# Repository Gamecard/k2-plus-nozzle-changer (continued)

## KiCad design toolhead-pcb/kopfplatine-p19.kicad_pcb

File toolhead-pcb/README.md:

# Kopfplatine P19, Fassung 10 – Toolhead-Platine für den K2-Düsenwechsler

**English summary:** This is the toolhead board for the K2 Plus nozzle changer (prototype 19 v2). It replaces the original
toolhead board, runs from 24–48 V, talks to the Klipper host via CAN bus and additionally provides USB through an on-board
4-port hub (bed camera, Cartographer probe, MCU). It carries an STM32G0B1 MCU, a TMC5160 stepper driver with external MOSFETs,
a 24-bit load-cell ADC, an accelerometer, five low-side outputs and all sensor inputs on 14 locking JST GH connectors.
The KiCad files are produced by a Python generator (`bauen.sh`); Gerber, BOM and CPL files for JLCPCB are included.
Status: not yet manufactured or tested.

Stand: Schaltplan und Layout sind vollständig und bestehen die automatischen Prüfungen; gefertigt oder in Betrieb genommen
wurde die Platine noch nicht. Lizenz und Haftung: [`../LIZENZ-UND-HAFTUNG.md`](../LIZENZ-UND-HAFTUNG.md).

## Aufgabe

Die Platine sitzt hinten am Druckkopf des Düsenwechslers (siehe [`../prototyp-19v2/README.md`](../prototyp-19v2/README.md)) und
ersetzt die Original-Kopfplatine des Creality K2 Plus. Sie steuert alles, was am Kopf selbst sitzt: den Extrudermotor, die
Hubmagnete des Riegels, die Lüfter, den Linienlaser, und sie liest alle Kopfsensoren. Die Heizungen und Temperaturfühler der
Patronen hängen **nicht** an dieser Platine, sondern an einer eigenen Heizplatine (nicht Teil dieses Repositorys).

Eckdaten: 52 × 76,8 mm, 6 Kupferlagen, beidseitig bestückt (230 Teile), Bauhöhe auf der Oberseite höchstens 7,37 mm, auf der
Unterseite flächig höchstens 1,5 mm. Vier Befestigungslöcher für M2 (H1–H4).

**Begriffe:**
- **CAN-Bus:** robuste Zweidraht-Datenleitung (CANH/CANL), über die Klipper mit Zusatzplatinen spricht; an jedem Ende des Busses
  sitzt ein 120-Ω-Abschlusswiderstand.
- **Low-Side-Schalter:** Ein Transistor (MOSFET) schaltet die Minusleitung eines Verbrauchers; die Plusleitung liegt fest an 24 V.
- **Lötbrücke (JP_…):** zwei Lötflächen, die man mit einem Lötzinntropfen verbindet oder mit einem Messer trennt, um eine Option zu wählen.
- **Nutzen (Panel):** Rahmen um die Platine, in dem sie gefertigt und bestückt wird; nach der Bestückung bricht man sie an
  **Haltestegen** mit **Mausbissen** (Reihen kleiner Bohrungen) heraus.

## Blockübersicht

Belege: [`SCHALTUNG.md`](SCHALTUNG.md) (Abschnitte 0f, 0h, 1–11), Schaltplan [`doku/schaltplan.pdf`](doku/schaltplan.pdf),
Stückliste [`fertigung/stueckliste.csv`](fertigung/stueckliste.csv). Bei Widersprüchen gilt der Schaltplan.

| Block | Bauteile | Aufgabe |
|---|---|---|
| **Eingang** | J1 (JST ZE 6-pol.), F1 (SMD-Sicherung 5 A / 63 V), D1 (TVS-Diode SMBJ51A), Dämpfungsglied und Pufferkondensatoren 100 V | Versorgung 24–48 V (höchstens 50 V) und CAN-Bus über einen Stecker. Bei Verpolung leitet D1 und die Sicherung löst aus. Spannungsmessung von VIN an der MCU |
| **24-V-Schiene** | U2 TPS54360 (Abwärtswandler 60 V), L1 33 µH, D3 | erzeugt V24 (≈ 23,8 V) für Hubmagnete, Lüfter, Laser und den 5-V-Wandler; Auslegung 2 A; Spannungsmessung an der MCU |
| **5 V / 3,3 V** | U3 LMR51420 (aus V24), U4 LDO ME6211 3,3 V | V5 für USB-Geräte, CAN-Transceiver und LED-Kette; V3V3 für Logik. Der 3,3-V-Regler wird über ein Dioden-ODER aus V5 oder aus der USB-C-Buchse gespeist (Flashen ohne 24 V); USB-C-Spannung geht nie auf V5. Analoge 3,3 V (AVDD) über Ferrit gefiltert |
| **CAN** | U10 TJA1051T/3, D_CAN (ESD), JP_CAN | CAN-Transceiver an PB0/PB1; 120-Ω-Abschluss über Lötbrücke JP_CAN (Werkzustand offen – schließen, wenn der Kopf Busende ist) |
| **USB-Eingang und Hub** | J44, D8 (ESD), U5 CH334P (4-Port-Hub, 12-MHz-Quarz Y1) | USB vom Steuerrechner über J44 an den Hub-Eingang. Hub-Ports: 1 → MCU (über U11), 2 → Bettkamera J42, 3 → Cartographer J43, 4 frei. VBUS an J44 dient nur der Erkennung „Kabel steckt“; die Geräte werden aus dem eigenen V5 über je eine selbstrückstellende Sicherung (PTC 0,5 A, F2/F3) versorgt |
| **USB-C zum Flashen** | J16 (USB-C liegend), D_C1 (ESD), U11 FSUSB42MUX | Steckt ein PC an J16, schaltet U11 die USB-Leitung der MCU vom Hub auf die USB-C-Buchse um; die MCU kann das am Pin PD3 erkennen |
| **Mikrocontroller** | U1 STM32G0B1RBT6 (LQFP-64), Quarz 8 MHz (Y2), Taster RESET (SW1) und BOOT (SW2), SWD-Messpads | führt Klipper (Firmware-Einstellung „CAN bus on PB0/PB1“ oder USB) |
| **Motortreiber** | U7 TMC5160A-TA, Q1–Q8 CSD19537Q3 (100-V-MOSFETs), R36/R43 0,11-Ω-Messwiderstände, J3 | Schrittmotortreiber mit externen MOSFETs, direkt aus VIN (24–48 V) versorgt; Step/Dir + SPI |
| **Wägezelle (PRTouch)** | U8 ADS1220 (24-bit-ADC), Eingangsfilter, J33 | wertet die Original-Messplatte (Dehnungsmessstreifen) des K2 Plus aus; ratiometrische Messung mit AVDD als Erregung |
| **Beschleunigungssensor** | U9 LIS2DW12 | für Input Shaping, am SPI-Bus |
| **Schaltausgänge** | Q9–Q13 AO3400A, Freilaufdioden, Gate-Pulldowns 100 kΩ | Low-Side für: Hubmagnete (beide gemeinsam), Kopflüfter L, Kopflüfter R, Bauteillüfter, Laser. Alle Ausgänge sind nach einem Reset aus. Laser-Plus über JP_LASER wählbar 5 V oder 24 V |
| **Sensoreingänge** | Hall G1 (digital), Hall G2 (analog + Komparator U13 TLV1701), Eddy-Spule LDC1612 (I²C), Probe/Endstop, 3 Lüfter-Tachos, NTC (Kopftemperatur), ESD-Arrays D18/D19 | Probe-Versorgung über JP_PROBE_V wählbar 5 V (Werk) oder 24 V; der Probe-Eingang verträgt 5 V und 24 V am Signal |
| **LED-Kette** | U12 SN74AHCT1G125 (Pegelwandler 3,3 → 5 V), F_LED (PTC 1,1 A), C_LED, J34 | adressierbare RGB-LEDs (WS2812B/SK6812) als Statusanzeige |
| **Statusanzeige** | D6, D11 (grün), D7, D14 (gelb) | Spannungen, Hubmagnet, Lebenszeichen der MCU |

## Stecker

Lage in mm auf der Bestückungsoberseite, gemessen von der linken oberen Platinenecke (x nach rechts, y nach unten); das ist die
Ansicht **von hinten auf den Kopf**. Alle JST-GH-Stecker (Raster 1,25 mm) liegen flach, rasten ein und nehmen fertig
konfektionierte Kabel auf; Pin 1 ist im Bestückungsdruck mit einem Dreieck markiert. Vollständige Belegung je Pin:
[`SCHALTUNG.md`](SCHALTUNG.md), Abschnitt **0h** (J30–J44) und **0f** (J1, J3, J16).

| Stecker | Typ / Pole | Funktion | Lage x / y, Abgang | Belegung (Kurzform) |
|---|---|---|---|---|
| J1 | JST ZE, 6 | Versorgung 24–48 V + CAN | 42,8 / 6,6, Oberkante | 1, 2 VIN · 3, 4 GND · 5 CANH · 6 CANL |
| J3 | JST ZE, 4 | Extrudermotor | 14,8 / 59,4, unten links | 1 A1 · 2 A2 · 3 B1 · 4 B2 |
| J16 | USB-C, liegend | PC-Anschluss zum Flashen | 8,4 / 3,3, Öffnung über die Oberkante | USB 2.0, CC je 5,1 kΩ |
| J30 | JST GH, 2 | Hubmagnet R | 34,1 / 17,9, Litzen nach oben | 1 +24 V · 2 geschaltet |
| J31 | JST GH, 3 | Hubmagnet L | 42,8 / 15,9, Litzen nach oben | 1 +24 V · 2 geschaltet · 3 frei |
| J32 | JST GH, 3 | Hall G1 (Riegel zu/offen) | 27,2 / 17,5, Litzen nach oben | 1 3,3 V · 2 GND · 3 Signal |
| J33 | JST GH, 4 | Messplatte (PRTouch) | 30,3 / 3,8, Litzen nach oben | 1 E+ · 2 E− · 3 S+ · 4 S− |
| J34 | JST GH, 3 | LED-Kette | 4,4 / 17,5, Litzen nach oben | 1 5 V · 2 GND · 3 Daten |
| J35 | JST GH, 3 | Probe / Endstop | 12,0 / 17,5, Litzen nach oben | 1 Versorgung (5 V / 24 V) · 2 GND · 3 Signal |
| J36 | JST GH, 3 | Kopflüfter R | 19,6 / 17,5, Litzen nach oben | 1 +24 V · 2 geschaltet · 3 Tacho |
| J37 | JST GH, 3 | Kopflüfter L | 24,9 / 66,6, Litzen nach unten | 1 +24 V · 2 geschaltet · 3 Tacho |
| J39 | JST GH, 2 | Linienlaser | 3,3 / 68,9, Litzen nach unten | 1 + (5 V / 24 V) · 2 geschaltet |
| J40 | JST GH, 5 | Eddy-Spule (LDC1612, I²C) | 13,9 / 29,3, Litzen nach unten | 1 3,3 V · 2 GND · 3 SCL · 4 SDA · 5 INTB |
| J41 | JST GH, 6 | Hall G2 (Arm) + Bauteillüfter | 30,9 / 60,6, Litzen nach unten | 1 Hall-Signal · 2 3,3 V · 3 GND · 4 Tacho · 5 geschaltet · 6 +24 V |
| J42 | JST GH, 5 | USB Bettkamera | 33,7 / 66,6, Litzen nach unten | 1 5 V · 2 GND · 3 D− · 4 D+ · 5 GND |
| J43 | JST GH, 5 | USB Cartographer | 42,8 / 70,0, Litzen nach unten | 1 5 V · 2 GND · 3 D− · 4 D+ · 5 GND |
| J44 | JST GH, 5 | USB-Eingang vom Steuerrechner | 19,1 / 3,8, Litzen nach oben | 1 VBUS (nur Erkennung) · 2 GND · 3 D− · 4 D+ · 5 GND |

„geschaltet“ = Minusleitung über den Low-Side-Schalter. J38 ist nicht belegt (die Nummer entfiel).

**Steckreihenfolge** (sonst verdeckt ein Gegenstecker den nächsten): **J39 vor J3**, **J42 vor J37**, **J44 vor J36**.
Alle übrigen Stecker sind in beliebiger Reihenfolge steckbar.

**Achtung:** Eingangsspannung höchstens 50 V (ein 48-V-Netzteil nicht höher drehen). J1 nicht unter Spannung stecken.

## Wegfall des Original-Kopfkabels (J2)

Frühere Fassungen hatten einen Anschluss J2 für das Original-Kopfkabel des K2 Plus. In Fassung 10 ist er **entfallen**, weil sonst
nicht alle Stecker flach und steckbar auf die Platine passten. Folgen:

- Für den Betrieb ist ein **neues Kabel vom Drucker zum Kopf** nötig:
  - an **J1**: Versorgung 24–48 V (2 Adern), GND (2 Adern), CANH, CANL;
  - an **J44**: USB vom Steuerrechner (D+, D−, GND; VBUS nur zur Erkennung).
- Entfallen sind damit auch: Betrieb und 24-V-Einspeisung über das Original-Kopfkabel, die Messpunkte für dessen serielle
  Leitungen und die zugehörigen Auswahl-Widerstände.
- Ist der Kopf das Ende des CAN-Busses, die Lötbrücke **JP_CAN** schließen.

## Kabel

Die Geräteleitungen, ihre Längen im Kopfmodell und empfohlene Fertigkabel stehen in [`doku/KABELLISTE.md`](doku/KABELLISTE.md).
Kurz: JST-GH-Fertigkabel (Gegenstecker GHR-0nV-S, Litze AWG 28), eine Seite mit Stecker, die andere offen zum Anlöten am Gerät.
Neben der Platine (Seitenstreifen 1,5 mm) die Litzen einzeln flach nebeneinander legen, kein rundes Bündel. Längen vor dem Kauf
am gedruckten Kopf nachmessen.

## Fertigung (JLCPCB)

Alle Angaben für das Bestellformular stehen in [`fertigung/bestellangaben.md`](fertigung/bestellangaben.md). Das Wichtigste:

| Punkt | Wert |
|---|---|
| Hochladen | `fertigung/nutzen/kopfplatine-p19-nutzen_gerber_jlcpcb.zip`, dazu `fertigung/nutzen/jlcpcb_bom.csv` und `fertigung/nutzen/jlcpcb_cpl.csv` |
| Nicht hochladen | `fertigung/kopfplatine-p19_gerber_jlcpcb.zip` (Einzelplatine ohne Rand – Stecker stehen näher als 3 mm an der Kante, JLC würde eigene Ränder ansetzen) |
| Lagen / Aufbau | 6 Lagen, Lagenaufbau JLC06161H-7628, 1,6 mm, ENIG, Durchkontaktierungen gefüllt und abgedeckt (Epoxy Filled & Capped) |
| Nutzen | „Panel by Customer“, 71 × 90,8 mm, eine Platine je Nutzen, Frässchlitz 2 mm, 5 Haltestege mit Mausbissen, 3 Passermarken, 3 Werkzeuglöcher |
| Impedanz | USB-Paare auf Lage 3 (In2.Cu) 0,20 mm / 0,15 mm, Ziel 90 Ω differentiell ±10 % (rechnerisch 83–91 Ω; Werkzeug `werkzeuge/zdiff_l3.py`) – JLC rechnet nach und fragt zurück |
| Bestückung | beidseitig, 230 Teile (87 oben, 143 unten), 78 BOM-Zeilen; Röntgenprüfung für Q1–Q8, U5, U9 empfohlen; unbestückt (DNP): C27, C28, C29, R21 |

Vor der Bestellung unbedingt:

- **Bestand des 2-poligen JST-GH-Steckers (LCSC C189893)** für J30 und J39 am Bestelltag prüfen – am 21.11.2026 waren nur 3 Stück
  vorrätig (2 je Platine). Sonst Beschaffung über den Bestücker, Beistellung oder von Hand nachbestücken.
- **Pin 1 und Drehung** aller gepolten Teile in der Bestellvorschau ansehen, besonders die JST-GH-Stecker J30–J44, J1, J3 und die
  Lage von J16. Nur 20 der 230 Teile sind gegen Bibliotheksdaten des Bestückers nachgewiesen
  ([`fertigung/drehung-nachweis.txt`](fertigung/drehung-nachweis.txt), 0 Fehler); die Liste der Teile, die von Hand zu prüfen
  sind, steht in den Bestellangaben, Abschnitt 5. Hilfe: [`fertigung/nutzen/pin1-liste.txt`](fertigung/nutzen/pin1-liste.txt).
- Lagerbestand aller knappen Teile prüfen; einige LCSC-Nummern sind nicht bestätigt (Liste am Ende von
  [`STUECKLISTE.md`](STUECKLISTE.md)).

## Inhalt dieses Ordners

| Pfad | Inhalt |
|---|---|
| `kopfplatine-p19.kicad_pro/_sch/_pcb/_dru` | KiCad-10-Projekt (Schaltplan, geroutete Platine, Zusatzregeln) |
| `kopfplatine_p19.kicad_sym`, `kopfplatine_p19.pretty/`, `fp-lib-table`, `sym-lib-table` | Projektbibliothek (eigene Symbole und Footprints); alles andere aus den KiCad-Standardbibliotheken |
| `SCHALTUNG.md` | pin-genaue Schaltungsvorgabe für den Generator (mit Lesehinweis oben) |
| `STUECKLISTE.md` | Stückliste mit Lagerstand und Bauhöhen (vom Generator erzeugt, Lagerstand vom November 2026) |
| `bauen.sh`, `generator/`, `werkzeuge/` | Generator: erzeugt Schaltplan, Platzierung, Prüfungen und Fertigungsdaten |
| `routing/` | Eingabe (`f10a_a.dsn`) und Ergebnis (`f10a_a.ses`) des gewählten Autorouter-Laufs |
| `fertigung/` | Gerber-ZIPs (Einzelplatine und Nutzen), BOM, CPL, Stückliste, Bestellangaben, Drehungsnachweis, Randabstand, Stege, Nutzen-Prüfung |
| `doku/` | Kabelliste, Schaltplan-PDF, Lagen-PDF, Bestückungsübersicht (PDF/PNG), Bilder, Prüfberichte |
| `klipper/` | Klipper-Beispielkonfiguration (Entwurf, nicht erprobt) |

## Platine neu erzeugen

Die KiCad-Dateien sind **nicht von Hand gezeichnet**, sondern werden von einem Python-Generator erzeugt. Änderungen gehören in
den Generator (`generator/kopfplatine.py` und Module); Änderungen nur in KiCad gehen beim nächsten Lauf verloren.

Benötigt (aus `bauen.sh` und dem Generator abgelesen):

- **KiCad 10** mit `kicad-cli` und dem Python-Modul `pcbnew` (Fertigungsdaten erstellt mit KiCad 10.0.8), KiCad-Standardbibliotheken
  in den üblichen Pfaden (`/usr/share/kicad/…`, Variablen `KICAD10_*`);
- **Python 3** mit `numpy` und `Pillow`;
- **rsvg-convert** (librsvg) für die Bilder;
- **gcc** (optional; beschleunigt die Wegsuche, sonst läuft eine Python-Fassung);
- **Freerouting** für das Routing (wird nicht von `bauen.sh` aufgerufen).

Ablauf:

```sh
cd toolhead-pcb
./bauen.sh                               # Schaltplan, ERC, Netzliste, Stückliste, Platzierung, Prüfungen, DSN für den Router
# Routing mit Freerouting auf ausgabe/kopfplatine-p19.dsn  ->  .ses-Datei
./bauen.sh fertig routing/f10a_a.ses     # Flächen, Nachverdrahtung, DRC, Gerber, BOM/CPL, Nutzen, Bestellangaben, Bilder
```

Ausgaben landen in `ausgabe/`, Zwischenstände in `zwischen/` (beide nicht im Repository). Der Generator ist auf gleiche Ergebnisse
bei jedem Lauf ausgelegt (`PYTHONHASHSEED=0`, fester Startwert für KiCads Element-Kennungen). Die mitgelieferte SES-Datei passt nur
zur DSN genau dieses Stands; nach jeder Änderung am Generator ist ein neuer Routing-Lauf nötig.

**Reproduzierbarkeit:** KiCad öffnet ein Projekt schreibgeschützt, sobald daneben eine Sperrdatei (`~….kicad_pro.lck`) liegt,
und vergibt dann interne Kennungen in anderer Folge – das änderte früher die Vorverlegung. `bauen.sh` und der Generator legen
deshalb während des Baus selbst eine neutrale Sperrdatei an und entfernen sie am Ende wieder. Geprüft am 22.11.2026 mit
KiCad 10.0.8 in sauberen Kopien: mit und ohne vorhandene Sperrdatei entsteht dieselbe Router-Eingabe; sie ist bis auf die erste
Zeile (Dateiname des Exports) gleich `routing/f10a_a.dsn`, die mitgelieferte SES passt also.

Bekannte Einschränkungen beim Neubau:

- Der Drehungsnachweis braucht die Bibliotheksdaten des Bestückers, die nicht im Repository liegen; vorher laden:
  `python3 -I werkzeuge/drehung/easyeda_holen.py werkzeuge/drehung/roh/easyeda fertigung/jlcpcb_bom.csv`
  (Einzelheiten [`werkzeuge/drehung/LIESMICH.txt`](werkzeuge/drehung/LIESMICH.txt)).
- Die zwei Prüfskripte für Randabstand (JLC-Regeln) und Pin-1-Liste liegen in `werkzeuge/` (`randabstand_pruefen.py`,
  `pin1_liste.py`); `./bauen.sh fertig routing/f10a_a.ses` lief damit in einer sauberen Kopie vollständig durch.
- Der Fertig-Schritt ist nicht ganz bitgleich wiederholbar: Kleine Stücke der Nachverdrahtung können um Bruchteile eines
  Millimeters anders enden. Nach jedem Neubau DRC und Prüfberichte ansehen.

Weitere Hilfswerkzeuge in `werkzeuge/`: `bestueckungsbild.py` (farbige Bestückungsübersicht beider Seiten, erzeugt
`doku/bilder/bestueckung_*.png`), `zdiff_l3.py` (Impedanz der USB-Paare, 2D-Feldrechnung), `uebersicht.py`
(Platzierung nach Funktionsblöcken einfärben), `bild2.py` und `liste.py` (Ausschnittbilder und Listen von Pads/Bahnen),
`easyeda_import.py` (Footprint-Geometrie aus Bibliotheksdaten ableiten; schreibt nur die abgeleiteten Maße nach
`generator/fremd_footprints.json`), `vorverlegung_nur.sh` (nur Vorverlegung und Prüfungen auf vorhandener Platzierung).

## Prüfstand

Berichte in [`doku/pruefberichte/`](doku/pruefberichte/) und [`fertigung/`](fertigung/):

| Prüfung | Ergebnis |
|---|---|
| ERC (Schaltplan) | 0 Fehler, 0 Warnungen |
| Netzlisten-Wächter | 162 Netze, 254 Bauteile; Netzliste Pin für Pin gleich der Soll-Netzliste; 286 IC- und Steckerpins gegen die Tabellen in `SCHALTUNG.md` geprüft |
| DRC (Platine, mit Schaltplan-Abgleich) | **0 Fehler**, 2 Warnungen: Bestückungsdruck der USB-C-Buchse J16 an der Platinenkante abgeschnitten (gewollt, die Buchse ragt über die Kante); 0 nicht verbundene Pads; Schaltplan-Abgleich 0 Abweichungen |
| Leistungsnetze | kein Stück schmaler als die Mindestbreite der Netzklasse; Motor-Strompfade fest in voller Breite verlegt |
| Kritische Netze (Längen, Durchkontaktierungen, Breiten, USB-Paare) | alle bestanden, eine begründete Abweichung (siehe unten) |
| Nutzen | alle Prüfungen bestanden (Kontur, Schlitzbreite, Stege, Mausbisse, Abstände, Passermarken, Bestückungsdatei) |
| Drehungsnachweis | 0 Fehler bei 20 nachweisbaren Teilen; übrige gepolte Teile in der Bestellvorschau prüfen |

**Begründete Abweichung TMC_VSA → R27:** Die Leitung vom Pin VSA des Motortreibers zum Filterwiderstand R27 (3,3 Ω) ist 15,2 mm lang
und hat 3 Durchkontaktierungen; vorgegeben waren höchstens 12 mm und 2 Durchkontaktierungen. R27 führt nur den Gleichstrom des
VSA-Reglers (einige 10 mA); die Stützung übernimmt C41 direkt am Pin (6,3 mm, im Soll). Die Mehrlänge entspricht etwa 0,07 Ω
gegenüber 3,3 Ω und ist elektrisch ohne Bedeutung. Die Prüfgrenze ist dafür in `generator/kritisch.py` auf 16 mm / 3
Durchkontaktierungen gesetzt.

## Bekannte Annahmen und offene Punkte

- **Nicht gefertigt, nicht erprobt.** Funktion, Wärme, USB-High-Speed-Qualität und CAN-Betrieb sind nur rechnerisch bzw. nach
  Datenblatt ausgelegt.
- Die Kabelabgänge von Bauteillüfter, LED-Kette und Probe sowie die Kabellängen stammen aus dem Kopfmodell bzw. sind angenommen.
- Die Impedanz der USB-Paare ist nur gerechnet (vereinfachte 2D-Feldrechnung, εr 4,5).
- Sicherung F1: Werte laut Händlerbeschreibung, Datenblattprüfung offen.
- Einige LCSC-Nummern (LEDs, PTC F2/F3, Spule L2) stammen aus einer früheren Suche und sind vor der Bestellung zu bestätigen.
- Laser-Versorgung (JP_LASER) und Probe-Versorgung (JP_PROBE_V) vor dem ersten Einschalten passend zu den angeschlossenen Geräten
  einstellen.
- Die Klipper-Beispielkonfiguration in `klipper/` ist ein Entwurf vom 11.11.2026 (vor Fassung 10). Der Hinweis dort auf USB „über
  das Kopfkabel“ ist überholt – USB kommt in Fassung 10 über J44. Pins und Sektionen am Muster prüfen.
- Die ausführlichen Arbeitsnotizen zum Entwurf (Rechenwege, verworfene Varianten) sind nicht veröffentlicht. Kommentare im
  Generator verweisen teils darauf (z. B. „§12p“, „§F10-S1“).

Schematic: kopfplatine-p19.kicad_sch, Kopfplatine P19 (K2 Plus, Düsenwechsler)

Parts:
C1: 10 µF 100 V; C_1210_3225Metric; MPN GRM32EC72A106KE05L; LCSC C576517
C2, C3, C4: 2,2 µF; C_1210_3225Metric; MPN HMK325B7225KN-T; LCSC C92775
C5, C6, C7, C8, C11, C14, C15, C17, C18, C24, C32, C34, C36, C39, C46, C48, C53, C55, C56, C60, C62, C63, C64, C65, C66, C67: 100 nF; C_0402_1005Metric; MPN CL05B104KB54PNC; LCSC C307331
C9: 15 nF; C_0402_1005Metric; MPN CC0402KRX7R9BB153; LCSC C114405
C10: 100 pF; C_0402_1005Metric; MPN 0402CG101J500NT; LCSC C1546
C12, C13, C16, C42: 10 µF; C_0805_2012Metric; MPN GRM21BR61H106KE43L; LCSC C440198
C19, C20: 22 µF; C_0805_2012Metric; MPN CL21A226MAQNNNE; LCSC C45783
C21, C25, C26, C35, C44, C45: 1 µF; C_0402_1005Metric; MPN CL05A105KO5NNNC; LCSC C29266
C22, C23, C30, C31, C33, C43, C54, C61: 10 µF; C_0603_1608Metric; MPN CL10A106KP8NNNC; LCSC C19702
C27, C28: 10 pF; C_0402_1005Metric; MPN CL05C100JB5NNNC; LCSC C32949; not fitted
C29: 100 nF; C_0402_1005Metric; MPN CL05B104KB54PNC; LCSC C307331; not fitted
C37, C38: 12 pF; C_0402_1005Metric; MPN 0402CG120J500NT; LCSC C1547
C40, C41: 100 nF; C_0805_2012Metric; MPN FM21X104K201ECG; LCSC C784084
C47: 22 nF; C_1206_3216Metric; MPN TCC1206X7R223K251FT; LCSC C282849
C49, C50, C51, C52: 220 nF; C_0402_1005Metric; MPN CC0402KRX5R8BB224; LCSC C326836
C57: 10 nF; C_0805_2012Metric; MPN CL21C103JBFNNNE; LCSC C27071
C58, C59: 1 nF; C_0402_1005Metric; MPN AC0402FRNPO9BN102; LCSC C20141842
C_D2, C_D3, C_D4: 10 µF; C_1210_3225Metric; MPN GRM32EC72A106KE05L; LCSC C576517
C_LED: 100 µF; C_1210_3225Metric; MPN CL32A107MPVNNNE; LCSC C23742
C_V24C, C_V24D: 10 µF; C_0805_2012Metric; MPN GRM21BR61H106KE43L; LCSC C440198
D1: SMBJ51A; D_SMB; MPN SMBJ51A; LCSC C163658
D2, D4, D20: BAT54SW; SOT-323_SC-70; MPN BAT54SWT1G; LCSC C78260
D3: SS310; D_SMA; MPN SS310; LCSC C7420364
D5, D12, D13, D15, D16, D17: B5819W; D_SOD-123; MPN B5819W SL; LCSC C8598
D6, D11: LED gruen; LED_0805_2012Metric; MPN KT-0805G; LCSC C2297
D7, D14: LED gelb; LED_0805_2012Metric; MPN KT-0805Y; LCSC C2296
D8, D9, D10: USBLC6-2SC6; SOT-23-6; MPN USBLC6-2SC6Y; LCSC C2969755
D18, D19: SRV05-4; SOT-23-6; MPN SRV05-4; LCSC C558418
D_C1: USBLC6-2SC6; SOT-23-6; MPN USBLC6-2SC6Y; LCSC C2969755
D_C2: B5819W; D_SOD-123; MPN B5819W SL; LCSC C8598
D_CAN: NUP2105L; SOT-23; MPN NUP2105LT1G; LCSC C14486
F1: 5 A 63 V DC; Fuse_1206_3216Metric; MPN 12H1500C; LCSC C2980745
F2, F3: PTC 0,5 A; Fuse_1812_4532Metric; MPN SMD1812P050TF/30; LCSC C12559
FB1, FB2: 600R; L_0603_1608Metric; MPN BLM18KG601SN1D; LCSC C85833
F_LED: PTC 1,1 A; Fuse_1812_4532Metric; MPN SMD1812P110TF; LCSC C3102
H1, H2, H3, H4: M2; Bohrung_2.4mm_Sperrkreis5.0mm
J1: ZE 6-pol.; JST_ZE_SM06B-ZESS-TB_1x06-1MP_P1.50mm_Horizontal; MPN SM06B-ZESS-TB(LF)(SN); LCSC C5306612
J3: ZE 4-pol.; JST_ZE_SM04B-ZESS-TB_1x04-1MP_P1.50mm_Horizontal; MPN SM04B-ZESS-TB(LF)(SN); LCSC C697811
J16: USB-C liegend; USB_C_Receptacle_HRO_TYPE-C-31-M-12; MPN TYPE-C-31-M-12; LCSC C165948
J30, J39: GH 2-pol.; JST_GH_SM02B-GHS-TB_1x02-1MP_P1.25mm_Horizontal_K2; MPN SM02B-GHS-TB(LF)(SN); LCSC C189893
J31, J32, J34, J35, J36, J37: GH 3-pol.; JST_GH_SM03B-GHS-TB_1x03-1MP_P1.25mm_Horizontal_K2; MPN SM03B-GHS-TB(LF)(SN); LCSC C514175
J33: GH 4-pol.; JST_GH_SM04B-GHS-TB_1x04-1MP_P1.25mm_Horizontal_K2; MPN SM04B-GHS-TB(LF)(SN); LCSC C189895
J40, J42, J43, J44: GH 5-pol.; JST_GH_SM05B-GHS-TB_1x05-1MP_P1.25mm_Horizontal_K2; MPN SM05B-GHS-TB(LF)(SN); LCSC C189896
J41: GH 6-pol.; JST_GH_SM06B-GHS-TB_1x06-1MP_P1.25mm_Horizontal_K2; MPN SM06B-GHS-TB(LF)(SN); LCSC C133065
JP_CAN: Lötbrücke offen; SolderJumper-2_P1.3mm_Open_RoundedPad1.0x1.5mm
JP_LASER: Laser V5/V24; SolderJumper-3_P1.3mm_Open_RoundedPad1.0x1.5mm
JP_PROBE_PU: Lötbrücke geschlossen; SolderJumper-2_P1.3mm_Bridged_RoundedPad1.0x1.5mm
JP_PROBE_V: J18 V5/V24; SolderJumper-3_P1.3mm_Bridged12_RoundedPad1.0x1.5mm
L1: 33 µH; L_Sunlord_SMS0850; MPN SMS0850-330MT; LCSC C7602869
L2: 4,7 µH; L_Changjiang_FXL0630; MPN FXL0630-4R7-M; LCSC C167220
Q1, Q2, Q3, Q4, Q5, Q6, Q7, Q8: CSD19537Q3; VSON-8_3.3x3.3mm_P0.65mm_NexFET; MPN CSD19537Q3; LCSC C478469
Q9, Q10, Q11, Q12, Q13: AO3400A; SOT-23; MPN AO3400A; LCSC C344010
R1: 100k 0,1%; R_0805_2012Metric; MPN PTFR0805B100KP9; LCSC C478884
R2: 5k6 0,1%; R_0402_1005Metric; MPN AT0402BRD075K6L; LCSC C5455509
R3: 120R; R_0402_1005Metric; MPN 0402WGF1200TCE; LCSC C25079
R4, R5, R80: 5k1; R_0402_1005Metric; MPN 0402WGF5101TCE; LCSC C25905
R6, R13, R16, R18, R20, R29, R30, R31, R56, R59, R63, R67, R71, R74, R75, R76, R79, R82, R83: 10k; R_0402_1005Metric; MPN 0402WGF1002TCE; LCSC C25744
R7: 20k; R_0402_1005Metric; MPN 0402WGF2002TCE; LCSC C25765
R8, R15, R23, R24, R55, R58, R62, R66, R70: 100k; R_0402_1005Metric; MPN 0402WGF1003TCE; LCSC C25741
R9: 470k; R_0805_2012Metric; MPN RC0805FR-07470KL; LCSC C89104
R10: 33k; R_0402_1005Metric; MPN 0402WGF3302TCE; LCSC C25779
R11: 240k; R_0402_1005Metric; MPN FRC0402F2403TS; LCSC C2909338
R12: 287k; R_0402_1005Metric; MPN FRC0402F2873TS; LCSC C5126158
R14: 7k5; R_0402_1005Metric; MPN 0402WGF7501TCE; LCSC C25918
R17: 73k2; R_0402_1005Metric; MPN 0402WGF7322TCE; LCSC C26986
R19, R25, R26, R52, R53, R60, R64, R68, R72, R73: 1k 0,1%; R_0402_1005Metric; MPN FRH0402B1001TS; LCSC C48533754
R21: 10k; R_0402_1005Metric; MPN 0402WGF1002TCE; LCSC C25744; not fitted
R27, R28: 3R3; R_0402_1005Metric; MPN FRC0402F3R30TS; LCSC C2933094
R32, R33, R34, R35, R39, R40, R41, R42, R50, R51: 10R; R_0402_1005Metric; MPN 0402WGF100JTCE; LCSC C25077
R36, R43: 0,11; R_2512_6332Metric; MPN LRBK25EFER110; LCSC C5121166
R37, R38, R44, R45, R46, R47, R48, R49: 47R; R_0402_1005Metric; MPN RC0402FR-0747RL; LCSC C137973
R54, R57, R61, R65, R69, R81: 100R; R_0402_1005Metric; MPN 0402WGF1000TCE; LCSC C25076
R77, R78: 2k2; R_0402_1005Metric; MPN 0402WGF2201TCE; LCSC C25879
R_D: 0,68; R_2512_6332Metric; MPN HoLRT2512-2W-680mR-1%; LCSC C5127855
SW1: RESET; SW_Alps_SKRPACE010_4.2x3.2mm; MPN SKRPACE010; LCSC C139797
SW2: BOOT; SW_Alps_SKRPACE010_4.2x3.2mm; MPN SKRPACE010; LCSC C139797
TH1: NTC 100k; R_0603_1608Metric; MPN SDNT1608X104F3950FTF; LCSC C919169
TP1: VIN; TestPoint_Pad_D1.0mm
TP2: CANH; TestPoint_Pad_D1.0mm
TP3: CANL; TestPoint_Pad_D1.0mm
TP4: V24; TestPoint_Pad_D1.0mm
TP5: V5; TestPoint_Pad_D1.0mm
TP6: 3V3; TestPoint_Pad_D1.0mm
TP7: AVDD; TestPoint_Pad_D1.0mm
TP10: DIO; TestPoint_Pad_D1.0mm
TP11: CLK; TestPoint_Pad_D1.0mm
TP12: RST; TestPoint_Pad_D1.0mm
TP13, TP14: GND; TestPoint_Pad_D1.0mm
U1: STM32G0B1RBT6; LQFP-64_10x10mm_P0.5mm; MPN STM32G0B1RBT6; LCSC C5143679
U2: TPS54360DDA; TI_SO-PowerPAD-8_ThermalVias; MPN TPS54360DDAR; LCSC C44377
U3: LMR51420YDDCR; SOT-23-6; MPN LMR51420YDDCR; LCSC C5383002
U4: ME6211C33M5G; SOT-23-5; MPN ME6211C33M5G-N; LCSC C82942
U5: CH334P; WCH_CH334P_QFN-16-1EP_3x3mm_P0.5mm_EP1.7x1.7mm; MPN CH334P; LCSC C5373042
U7: TMC5160A-TA; TQFP-48-1EP_7x7mm_P0.5mm_EP5x5mm; MPN TMC5160A-TA-T; LCSC C516354
U8: ADS1220IPWR; TSSOP-16_4.4x5mm_P0.65mm; MPN ADS1220IPWR; LCSC C48263
U9: LIS2DW12TR; ST_LIS2DW12_LGA-12_2x2mm_P0.5mm; MPN LIS2DW12TR; LCSC C189624
U10: TJA1051T/3; SOIC-8_3.9x4.9mm_P1.27mm; MPN TJA1051T/3; LCSC C5342108
U11: FSUSB42MUX; MSOP-10_3x3mm_P0.5mm; MPN FSUSB42MUX; LCSC C11355
U12: SN74AHCT1G125; SOT-23-5; MPN SN74AHCT1G125DBVR; LCSC C7484
U13: TLV1701AIDBVR; SOT-23-5; MPN TLV1701AIDBVR; LCSC C130035
Y1: 12 MHz; Crystal_SMD_3225-4Pin_3.2x2.5mm; MPN TAXM12M4RFBCCT2T; LCSC C133337
Y2: 8 MHz; Crystal_SMD_3225-4Pin_3.2x2.5mm; MPN TAXM8M4RDBCCT2T; LCSC C400090

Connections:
ADC_V24: C15.1, D4.3 (COM), R15.2, R16.1, U1.26 (PC5)
ADC_VIN: C5.1, D2.3 (COM), R1.2, R2.1, U1.25 (PC4)
ADS_CS: R47.2, U8.2 (~CS)
ADS_DIN: R48.2, U8.16 (DIN)
ADS_DOUT: R49.1, U8.15 (DOUT/~DRDY)
ADS_SCLK: R46.2, U8.1 (SCLK)
AVDD: C23.1, C24.1, C53.1, C54.1, FB1.2, R50.1, TP7.1, U8.12 (AVDD)
BMA1: C49.2, J3.1, Q1.1 (S), Q1.2 (S), Q1.3 (S), Q2.5 (D), U7.40 (BMA1)
BMA2: C50.2, J3.2, Q3.1 (S), Q3.2 (S), Q3.3 (S), Q4.5 (D), U7.37 (BMA2)
BMB1: C51.2, J3.3, Q5.1 (S), Q5.2 (S), Q5.3 (S), Q6.5 (D), U7.48 (BMB1)
BMB2: C52.2, J3.4, Q7.1 (S), Q7.2 (S), Q7.3 (S), Q8.5 (D), U7.45 (BMB2)
BOOT_24: C11.1, U2.1 (BOOT)
BOOT_TASTER: R25.1, SW2.2
CA1: C49.1, U7.42 (CA1)
CA2: C50.1, U7.35 (CA2)
CANH: D_CAN.1 (K), J1.5, R3.1, TP2.1, U10.7 (CANH)
CANL: D_CAN.2 (K), J1.6, JP_CAN.2 (B), TP3.1, U10.6 (CANL)
CAN_RX: U1.27 (PB0), U10.4 (RXD)
CAN_TERM: JP_CAN.1 (A), R3.2
CAN_TX: U1.28 (PB1), U10.1 (TXD)
CB1: C51.1, U7.2 (CB1)
CB2: C52.1, U7.43 (CB2)
CB_5: C18.1, U3.6 (CB)
COMP_24: C10.1, R14.1, U2.6 (COMP)
COMP_RC: C9.1, R14.2
CS_ADS: R47.1, U1.32 (PB12)
CS_LIS: U1.33 (PB13), U9.2 (CS)
CS_TMC: U1.21 (PA4), U7.13 (~CS/CFG3)
DIAG0: R30.2, U1.34 (PB14), U7.26 (SWN/DIAG0)
DIAG1: R31.2, U1.35 (PB15), U7.27 (SWP/DIAG1)
DIR: U1.31 (PB11), U7.18 (REFR/DIR)
DRDY_ADS: U1.15 (PC2), U8.14 (~DRDY)
DRV_ENN: R29.2, U1.29 (PB2), U7.28 (~DRV_EN)
EN_24: R9.2, R10.1, U2.3 (EN)
FB_5: R17.2, R18.1, U3.4 (FB)
FB_24: R12.2, R13.1, U2.5 (FB)
GND: C1.2, C2.2, C3.2, C4.2, C5.2, C6.2, C7.2, C8.2, C9.2, C10.2, C12.2, C13.2, C14.2, C15.2, C16.2, C17.2, C19.2, C20.2, C21.2, C22.2, C23.2, C24.2, C25.2, C26.2, C27.2, C28.2, C29.2, C30.2, C31.2, C32.2, C33.2, C34.2, C35.2, C36.2, C37.2, C38.2, C39.2, C40.2, C41.2, C42.2, C43.2, C44.2, C45.2, C46.2, C53.2, C54.2, C55.2, C58.2, C59.2, C60.2, C61.2, C62.2, C63.2, C64.2, C65.2, C66.2, C67.2, C_D2.2, C_D3.2, C_D4.2, C_LED.2, C_V24C.2, C_V24D.2, D1.2 (A), D2.1 (A), D3.2 (A), D4.1 (A), D6.1 (K), D7.1 (K), D8.2 (GND), D9.2 (GND), D10.2 (GND), D11.1 (K), D18.2 (VN), D19.2 (VN), D20.1 (A), D_C1.2 (GND), D_CAN.3 (A), J1.3, J1.4, J16.A1 (GND), J16.A12 (GND), J16.B1 (GND), J16.B12 (GND), J16.SH (SHIELD), J32.2, J34.2, J35.2, J40.2, J41.3, J42.2, J42.5, J43.2, J43.5, J44.2, J44.5, Q9.2 (S), Q10.2 (S), Q11.2 (S), Q12.2 (S), Q13.2 (S), R2.2, R4.2, R5.2, R7.2, R8.2, R10.2, R11.2, R13.2, R16.2, R18.2, R24.2, R36.2, R38.2, R43.2, R45.2, R51.2, R55.2, R58.2, R62.2, R66.2, R70.2, R75.2, SW1.2, TH1.2, TP13.1, TP14.1, U1.9 (VSS), U2.7 (GND), U2.9 (GNDPAD), U3.1 (GND), U4.2 (GND), U5.17 (GND), U7.6 (GNDA), U7.11 (TST_MODE), U7.12 (CLK), U7.19 (GNDD), U7.23 (ENCB/DCEN/CFG4), U7.24 (ENCA/DCIN/CFG5), U7.30 (GNDD), U7.49 (EP), U8.3 (CLK), U8.4 (DGND), U8.5 (AVSS), U9.6 (GND), U9.7 (RES), U9.8 (GND), U10.2 (GND), U10.8 (S), U11.5 (GND), U11.10 (OE#), U12.1, U12.3 (GND), U13.2 (V-), Y1.2 (G), Y1.4 (G), Y2.2 (G), Y2.4 (G)
G_HUB: Q9.1 (G), R54.2, R55.1
G_LASER: Q13.1 (G), R69.2, R70.1
G_LUEFTER_B: Q12.1 (G), R65.2, R66.1
G_LUEFTER_L: Q10.1 (G), R57.2, R58.1
G_LUEFTER_R: Q11.1 (G), R61.2, R62.1
HA1: R32.1, U7.41 (HA1)
HA1_G: Q1.4 (G), R32.2
HA2: R34.1, U7.36 (HA2)
HA2_G: Q3.4 (G), R34.2
HALL_G1: D18.1 (IO1), J32.3, R71.2, R72.1
HALL_G1_F: C62.1, R72.2, U1.13 (PC0)
HALL_G2: D18.3 (IO2), J41.1, R73.1
HALL_G2_ADC: C63.1, R73.2, U1.17 (PA0), U13.1 (IN+)
HALL_G2_JN: R76.2, U1.14 (PC1), U13.4 (OUT)
HALL_SCHWELLE: R74.2, R75.1, U13.3 (IN-)
HB1: R39.1, U7.1 (HB1)
HB1_G: Q5.4 (G), R39.2
HB2: R41.1, U7.44 (HB2)
HB2_G: Q7.4 (G), R41.2
HUBMAGNET: R54.1, U1.57 (PB3)
HUB_3V3: C26.1, R21.1, U5.16 (VDD33)
HUB_RST: C29.1, R21.2, U5.13 (RESET#/CDP)
HUB_SCHALT: D12.2 (A), D13.2 (A), D14.1 (K), J30.2, J31.2, Q9.3 (D)
HUB_XI: C27.1, U5.2 (XI), Y1.1
HUB_XO: C28.1, U5.1 (XO), Y1.3
I2C_SCL: D18.4 (IO3), J40.3, R77.2, U1.62 (PB8)
I2C_SDA: D18.6 (IO4), J40.4, R78.2, U1.63 (PB9)
INT_LIS: U1.16 (PC3), U9.12 (INT1)
KABEL_ERKENNUNG: R23.2, R24.1, U1.52 (PD2)
LA1: R33.1, U7.39 (LA1)
LA1_G: Q2.4 (G), R33.2
LA2: R35.1, U7.38 (LA2)
LA2_G: Q4.4 (G), R35.2
LASER: R69.1, U1.58 (PB4)
LASER_PLUS: J39.1, JP_LASER.2 (C)
LASER_SCHALT: J39.2, Q13.3 (D)
LB1: R40.1, U7.47 (LB1)
LB1_G: Q6.4 (G), R40.2
LB2: R42.1, U7.46 (LB2)
LB2_G: Q8.4 (G), R42.2
LDC_INTB: D19.1 (IO1), J40.5, R79.2, U1.3 (PC13)
LED_3V3_A: D6.2 (A), R19.2
LED_24_A: D7.2 (A), R20.2
LED_DATEN: U1.59 (PB5), U12.2
LED_DATEN_5V: J34.3, R81.2
LED_DATEN_Y: R81.1, U12.4
LED_HUB_A: D14.2 (A), R56.2
LED_STATUS: R26.1, U1.47 (PA15)
LED_ST_A: D11.2 (A), R26.2
LUEFTER_B_SCHALT: D17.2 (A), J41.5, Q12.3 (D)
LUEFTER_L_SCHALT: D15.2 (A), J37.2, Q10.3 (D)
LUEFTER_R_SCHALT: D16.2 (A), J36.2, Q11.3 (D)
MCU_OSC_IN: C37.1, U1.10 (PF0), Y2.1
MCU_OSC_OUT: C38.1, U1.11 (PF1), Y2.3
MCU_USB_DM: U1.43 (PA9/PA11), U11.4 (D-)
MCU_USB_DP: U1.44 (PA10/PA12), U11.3 (D+)
MP_EMINUS: C56.2, J33.2, R51.1, U8.8 (REFN0)
MP_EPLUS: C56.1, J33.1, R50.2, U8.9 (REFP0)
MP_SMINUS: J33.4, R53.1
MP_SMINUS_F: C57.2, C59.1, R53.2, U8.10 (AIN1)
MP_SPLUS: J33.3, R52.1
MP_SPLUS_F: C57.1, C58.1, R52.2, U8.11 (AIN0/REFP1)
NRST: C39.1, SW1.1, TP12.1, U1.12 (PF2)
NTC_KOPF: R80.2, TH1.1, U1.18 (PA1)
PROBE_IN: C67.1, D20.3 (COM), R83.2, U1.64 (PC10)
PROBE_PU: JP_PROBE_PU.1 (A), R82.2
PROBE_SIG: J35.3, JP_PROBE_PU.2 (B), R83.1
PROBE_V: J35.1, JP_PROBE_V.2 (C)
PWM_BAUTEILLUEFTER: R65.1, U1.48 (PC8)
PWM_LUEFTER_L: R57.1, U1.38 (PC6)
PWM_LUEFTER_R: R61.1, U1.39 (PC7)
RT_24: R11.1, U2.4 (RT/CLK)
SPI1_MISO: R49.2, U1.23 (PA6), U7.16 (SDO/CFG0), U9.3 (SDO/SA0)
SPI1_MOSI: R48.1, U1.24 (PA7), U7.15 (SDI/CFG1), U9.4 (SDA/SDI/SDO)
SPI1_SCK: R46.1, U1.22 (PA5), U7.14 (SCK/CFG2), U9.1 (SCL/SPC)
SRA: Q2.1 (S), Q2.2 (S), Q2.3 (S), Q4.1 (S), Q4.2 (S), Q4.3 (S), R36.1, R37.2
SRB: Q6.1 (S), Q6.2 (S), Q6.3 (S), Q8.1 (S), Q8.2 (S), Q8.3 (S), R43.1, R44.2
STEP: U1.30 (PB10), U7.17 (REFL/STEP)
SWCLK: R25.2, TP11.1, U1.46 (PA14)
SWDIO: TP10.1, U1.45 (PA13)
SW_5: C18.2, L2.1, U3.2 (SW)
SW_24: C11.2, D3.1 (K), L1.1, U2.8 (SW)
TACHO_B: R68.2, U1.49 (PC9)
TACHO_B_K: J41.4, R67.2, R68.1
TACHO_L: R60.2, U1.40 (PD8)
TACHO_L_K: J37.3, R59.2, R60.1
TACHO_R: R64.2, U1.41 (PD9)
TACHO_R_K: J36.3, R63.2, R64.1
TMC_5V: C43.1, C44.1, R28.1, U7.5 (5VOUT)
TMC_12V: C42.1, U7.3 (12VOUT)
TMC_CPI: C47.2, U7.32 (CPI)
TMC_CPO: C47.1, U7.31 (CPO)
TMC_SRAH: R37.1, U7.8 (SRAH)
TMC_SRAL: R38.1, U7.7 (SRAL)
TMC_SRBH: R44.1, U7.9 (SRBH)
TMC_SRBL: R45.1, U7.10 (SRBL)
TMC_VCC: C45.1, R28.2, U7.29 (VCC)
TMC_VCP: C48.1, U7.34 (VCP)
TMC_VSA: C41.1, R27.2, U7.4 (VSA)
USBC_CC1: J16.A5 (CC1), R4.1
USBC_CC2: J16.B5 (CC2), R5.1
USBC_DM: D_C1.3 (I/O2), D_C1.4 (I/O2), J16.A7 (D-), J16.B7 (D-), U11.8 (HSD2-)
USBC_DP: D_C1.1 (I/O1), D_C1.6 (I/O1), J16.A6 (D+), J16.B6 (D+), U11.9 (HSD2+)
USBC_ERKANNT: R6.2, R7.1, R8.1, U1.53 (PD3), U11.2 (Sel)
USB_CAR_DM: D10.3 (I/O2), D10.4 (I/O2), J43.3, U5.5 (DM3)
USB_CAR_DP: D10.1 (I/O1), D10.6 (I/O1), J43.4, U5.6 (DP3)
USB_KAM_DM: D9.3 (I/O2), D9.4 (I/O2), J42.3, U5.7 (DM2)
USB_KAM_DP: D9.1 (I/O1), D9.6 (I/O1), J42.4, U5.8 (DP2)
USB_MCU_DM: U5.9 (DM1), U11.6 (HSD1-)
USB_MCU_DP: U5.10 (DP1), U11.7 (HSD1+)
USB_UP_DM: D8.3 (I/O2), D8.4 (I/O2), J44.3, U5.11 (DMU)
USB_UP_DP: D8.1 (I/O1), D8.6 (I/O1), J44.4, U5.12 (DPU)
V3V3: C7.1, C8.1, C22.1, C32.1, C33.1, C34.1, C46.1, C55.1, C60.1, C61.1, C64.1, D2.2 (K), D4.2 (K), D18.5 (VP), D19.5 (VP), D20.2 (K), FB1.1, FB2.1, J32.1, J40.1, J41.2, R19.1, R29.1, R30.1, R31.1, R59.1, R63.1, R67.1, R71.1, R74.1, R76.1, R77.1, R78.1, R79.1, R82.1, SW2.1, TP6.1, U1.6 (VBAT), U1.8 (VDD), U4.5 (VOUT), U7.20 (VCC_IO), U7.21 (SD_MODE), U7.22 (SPI_MODE), U8.13 (DVDD), U9.9 (VDD), U9.10 (VDDIO), U10.5 (VIO), U11.1 (VCC), U13.5 (V+)
V5: C6.1, C19.1, C20.1, C25.1, D5.2 (A), F2.1, F3.1, F_LED.1, JP_LASER.1 (A), JP_PROBE_V.1 (A), L2.2, R17.1, TP5.1, U5.15 (V5), U10.3 (VCC)
V5_LED: C65.1, C66.1, C_LED.1, F_LED.2, J34.1, U12.5 (VCC)
V24: C12.1, C13.1, C14.1, C16.1, C17.1, C_V24C.1, C_V24D.1, D12.1 (K), D13.1 (K), D15.1 (K), D16.1 (K), D17.1 (K), J30.1, J31.1, J36.1, J37.1, J41.6, JP_LASER.3 (B), JP_PROBE_V.3 (B), L1.2, R12.1, R15.1, R20.1, R56.1, TP4.1, U3.3 (VIN), U3.5 (EN)
VBUS2: J44.1, R23.1
VBUS_C: D_C1.5 (VBUS), D_C2.2 (A), J16.A4 (VBUS), J16.A9 (VBUS), J16.B4 (VBUS), J16.B9 (VBUS), R6.1
VBUS_CAR: C31.1, D10.5 (VBUS), F3.2, J43.1
VBUS_KAM: C30.1, D9.5 (VBUS), F2.2, J42.1
VIN: C2.1, C3.1, C4.1, C40.1, C48.2, D1.1 (K), F1.2, Q1.5 (D), Q3.5 (D), Q5.5 (D), Q7.5 (D), R1.1, R9.1, R27.1, R_D.1, TP1.1, U2.2 (VIN), U7.33 (VS)
VIN_DAEMPF: C1.1, C_D2.1, C_D3.1, C_D4.1, R_D.2
VIN_ROH: F1.1, J1.1, J1.2
VREFP: C35.1, C36.1, FB2.2, R80.1, U1.7 (VREF+)
V_LDO_EIN: C21.1, D5.1 (K), D_C2.1 (K), U4.1 (VIN), U4.3 (EN)

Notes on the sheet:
5 Mikrocontroller STM32G0B1RBT6 (USB über FSUSB42MUX, CAN PB0/PB1)
1 Eingang J1 24…50 V + CAN: Sicherung 5 A, SMBJ51A, VIN-Messung
1a CAN-Transceiver TJA1051T/3, ESD, 120-Ω-Abschluss über JP_CAN (Werk offen)
1b USB-C J16 (Flashen) + USB-Umschalter FSUSB42MUX (Sel = USBC_ERKANNT)
2 24-V-Schiene TPS54360 (VIN -> 23,8 V / 2 A, 404 kHz)
3 5 V (LMR51420, 1,1 MHz) und 3,3 V (LDO), AVDD-Filter
4 USB-Hub CH334P (Port 1 MCU, 2 Kamera J14, 3 Cartographer J15, 4 Reserve)
4 USB-Eingang J44 (ESD, Erkennung VBUS2 an PD2)
6 Motortreiber TMC5160A + 4 x 2 CSD19537Q3, Sense 2 x 0,11 Ω
7 Wägezelle ADS1220 (ratiometrisch, Eingangsfilter)
8/10 LIS2DW12, Hall G1/G2 + TLV1701, Eddy-I2C, NTC, ESD
9 Ausgänge: Hubmagnete, 3 Lüfter, Laser (Low-Side AO3400A, 100 kΩ Pulldown)
10a Neopixel (74AHCT1G125, PTC 1,1 A) und Reserve-Endstop/Probe J18
4a Gebündelte Kabelbaum-Stecker J20–J23 (JST GH liegend) [Fassung 2]
11 Messpads
Befestigung
ERC-Markierungen
Kopfplatine P19 (K2 Plus, Düsenwechsler) – Fassung 10 – 21.11.2026
FASSUNG 10 – Schaltplan zur Platine (6 Lagen, liegende JST GH) – Vorgabe SCHALTUNG.md, Rechenwege SCHALTPLAN-NOTIZEN.md
Versorgung 24…48 V + CAN über J1 (JST ZE 6-pol.). USB vom Host über J44 (VBUS2 nur Erkennung, nie an V5). Kein Kopfkabel J2. Lötbrücken: Werkzustand im Wert/Bemerkung. Verbindungen nur über gleichnamige globale Labels.

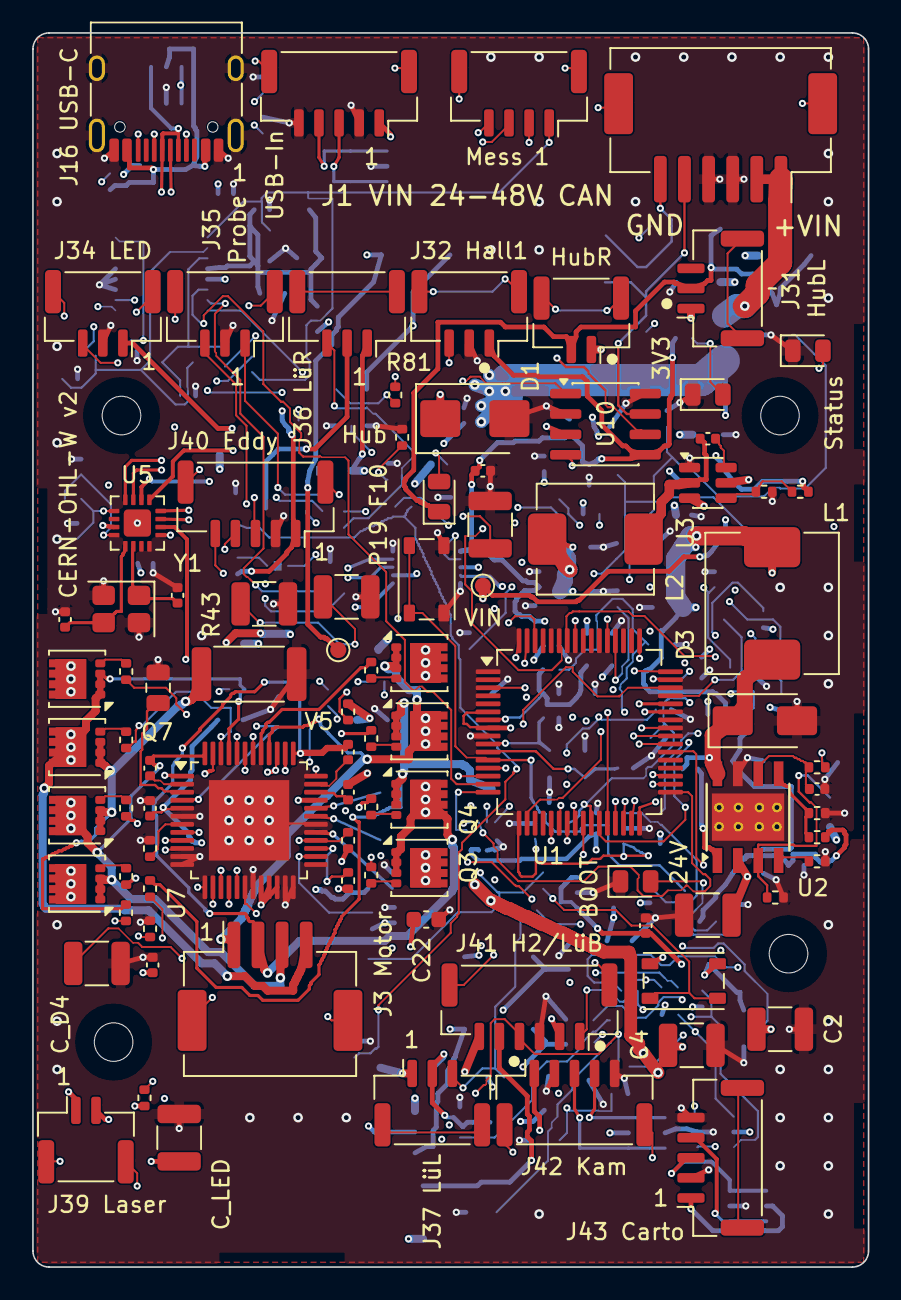
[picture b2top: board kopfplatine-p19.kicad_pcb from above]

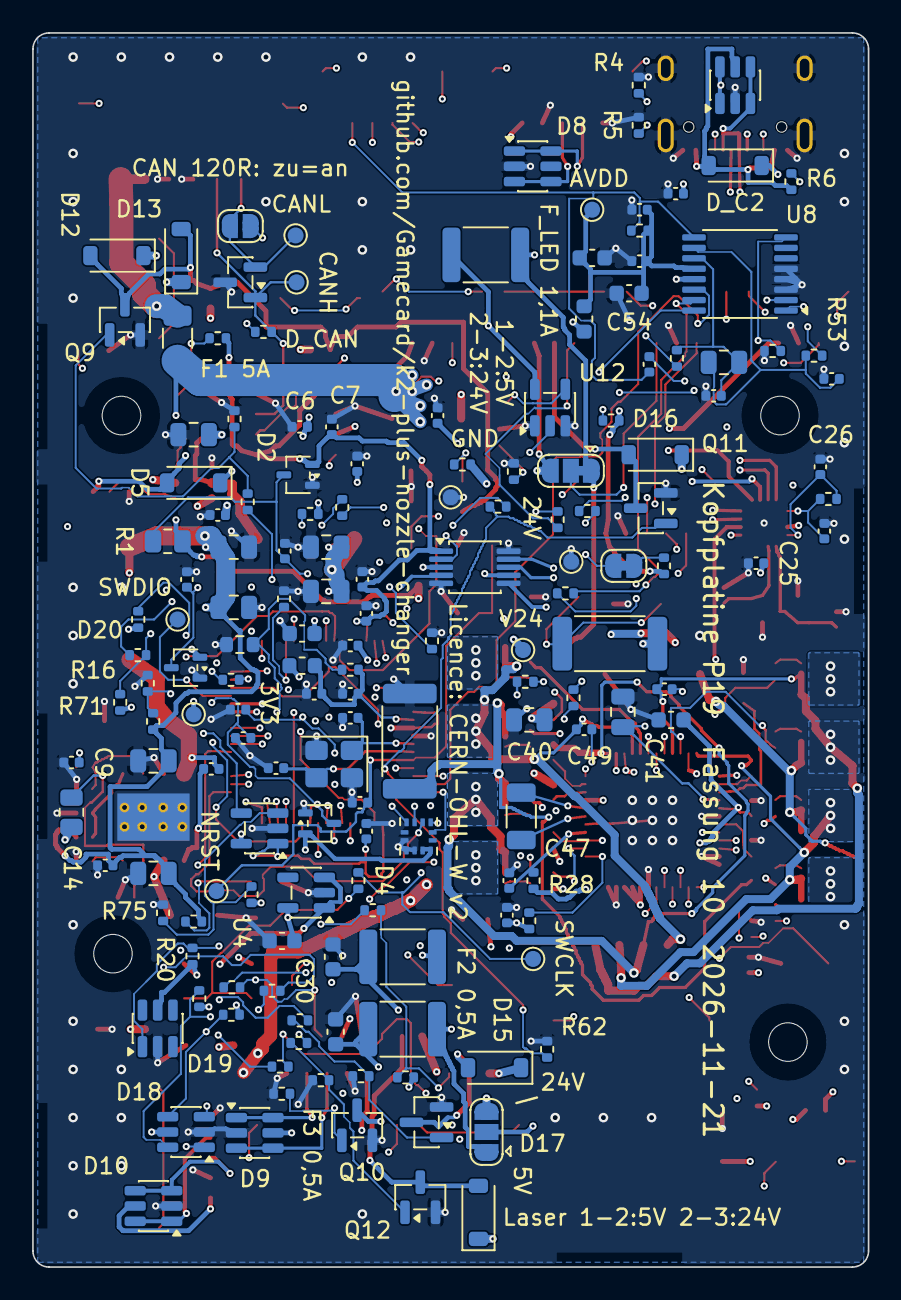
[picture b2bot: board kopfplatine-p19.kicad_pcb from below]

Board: 6 copper layers, 52.0 x 76.8 mm, 254 parts (159 on the bottom side), 162 nets.

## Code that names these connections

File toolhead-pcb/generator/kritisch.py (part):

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                           "bleibt beim Router – Grenzwert gilt nach dem Routing"}
# Abweichungen vom Auftrag 12o (Grenzwert der Prüfung ≠ Wunsch), mit Grund – erscheinen im Bericht hinter dem Urteil
ABWEICHUNG = {
    ("TMC_5V", "C43"): "Auftrag ≤ 5 mm: nicht erreichbar – am Pin steht C44 (1,1 mm); C43 kann unten erst über der Via-Reihe der oberen Pins stehen",
    ("TMC_VSA", "C41"): "Auftrag ≤ 5 mm: nicht erreichbar – Pins 3/4/5 liegen nebeneinander, neben den Pins ist nur Platz für EIN Teil (C44)",
    ("TMC_12V", "C42"): "Auftrag ≤ 5 mm: nicht erreichbar – einzige Gasse oben zwischen U7 und der Bauteilspalte, C42 (0805) passt erst über U7",
    ("TMC_VCC", "C45"): "Auftrag ≤ 5 mm: nicht erreichbar – Unterseite unter U7 und 1,2 mm Ring bleiben für die Durchkontaktierungen der Pins frei",
    ("VREFP", "Abstand"): "Auftrag ≥ 3 mm: nicht erreichbar – der Pin U1-7 selbst liegt 1,7 mm neben dem festen Motorpfad BMA1",
}
# [F10] Fassung 10 (liegende JST GH, R28 verschoben): der Längswiderstand R27 des VSA-Filters wird nach dem Routing mit 15,2 mm /
#   3 Vias erreicht (Läufe f10a: a 15,2/3, d 13,6/2, b 11,7/2 mit Engstelle 0,11 mm, c 22,0). Grenze dafür 16 mm / 3 Vias: R27 führt
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if _os.environ.get("K2_F9", "1") == "1" and _os.environ.get("K2_F10", "1") == "1":
    _b, _z, _s = KRIT["TMC_VSA"]
    KRIT["TMC_VSA"] = (_b, [(r, p_, 16.0, 3, w) if r == "R27" else (r, p_, l, v, w) for r, p_, l, v, w in _z], _s)
    ABWEICHUNG[("TMC_VSA", "R27")] = ("Auftrag ≤ 12 mm / 2 Vias: in Fassung 10 nicht erreicht – Gleichstromglied, Stützung C41 am Pin; "
                                      "Grenze 16 mm / 3 Vias (siehe STAND-ROUTING.md 22.11.2026)")
# USB-Paare: Name, (P-Netz, N-Netz), Art, Längenunterschied max mm, Vias max je Ader; HS zusätzlich: nur Lagen mit
#   GND-Nachbarlage (L1/L3 an L2) und keine Lücke der Bezugsfläche unter dem Paar
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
